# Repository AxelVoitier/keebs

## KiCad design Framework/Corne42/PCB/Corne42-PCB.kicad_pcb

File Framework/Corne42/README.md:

# Corne42 / Framework 16 — design review prototype

**Not released for fabrication, assembly, flashing or installation. No physical prototype has been tested.**

This is an AI-assisted derivative of Axel Voitier's HandyWork and A1 templates,
with 42 One Key Modules in a Corne-inspired layout: 3 × 6 keys plus 3 thumb keys
per hand. It uses OKMs, **not Choc switches**. The Corne Chocolate reference supplies
key positions; the controller and electrical design come from HandyWork.
Horizontal pitch is increased from 19.05 to 20.30 mm to avoid OKM pad/tab collisions;
vertical pitch remains 19.05 mm, with each half shifted inward by 2 mm. This is
not an exact reproduction of every Corne variant or of its keycap dimensions.

KiCad rendering of the actual PCB and embedded OKM models. The aluminium top
plate and laptop chassis are not shown; this is not a photograph or a fit validation.

## Review entry points

- [Main PCB and schematic](PCB/Corne42-PCB.kicad_pro), with project-relative libraries
  in `../Corne42.pretty` and `../Corne42.kicad_sym`.
- [Aluminium plate](AluPlate/Corne42-AluPlate.kicad_pro).
- [Firmware source](Firmware), [matrix/LED mapping](Review/electrical-mapping.json).
- [DRC](Review/drc.json), [ERC](Review/erc.json), [plate DRC](Review/plate-drc.json).
- [Conditional height calculation](Review/height-budget-conditional.json),
  [aperture check](Review/plate-aperture-check.json).
- [BOM](Review/BOM-review-only.csv), [supplier CPL](Review/CPL-review-only.csv),
  [controller underside](Review/controller-assembly-detail.svg), all **review only**.

The existing HandyWork files and shared Framework libraries are unchanged.
The local footprint variants preserve the per-component geometry used in the
reviewed board; they are supplied for library parity, not as new general-purpose
footprints. The corrected OKM footprint from upstream main is the starting point.

## Digital evidence and its limits

KiCad 10.0.7: **zero DRC errors, zero unconnected items, zero schematic/PCB parity
violations and zero ERC errors** in the supplied reports. These are design-rule
and consistency results, not proof of functional hardware.

The 42 DRC warnings report mixed SMD signal pads and plated mechanical slots on
OKMs. The 24 ERC warnings report inherited `C_Small` library differences; the
prior review compared pin geometry and types. The reports retain these warnings.
The main board report has no ignored checks. The plate retains its inherited
ignored-check list, visible in its report. No findings are hidden by this PR.

The main PCB SHA256 is
`47739568c578cbd6d3d88ca0366ca4ee43947878c37bd59026879a236ae34019`;
the plate SHA256 is
`d6a3a7b0d626e86c300b75459d5cb854e0ef8071d36dce5748283f1038d9d137`.
The reports predate this packaging step; the native design files are byte-identical
to those checked. Fresh portability checks are documented in `Review/portability.json`.

## Questions before spending money on a prototype

1. **Mechanical seating and height are unresolved.** A conditional comparison of
   the OKM model with Framework's simplified carrier puts its underside 0.70 mm
   beyond a representative main-field boundary. Another calculated placement
   leaves only about 0.055 mm nominal vertical slack, before tolerances, solder,
   adhesive, insulation and flex. These are not verified support positions or a
   full 42-key collision test. The OKM contact-plane datum, actual PCB supports,
   pogo travel, underside clearance and lid clearance need independent review.
   No support-height change is proposed as a fix without those measurements.
2. **Finished thickness:** proposed main PCB 0.8 mm, 4 layers, ENIG; plate 0.8 mm
   aluminium-base PCB with copper on the bottom only, following the original
   build. The inherited main CAD stack totals 0.8192 mm and the plate has a
   1 mm/FR4 placeholder. These metadata are not a qualified fabrication stack.
   An explicit manufacturer stack and tolerances must replace the placeholders
   before release. Nominal 0.8 mm alone does not prove fit.
3. **Via process and assembly:** 40 drilled 0.30 mm holes overlap stencil openings
   ([coordinates](Review/paste-overlapping-drills.csv)). Filled/capped was a
   conservative quotation choice, not an established requirement from Axel.
   Can the original plugged/tented process be qualified here? The 168 plated
   mechanical slots and 6 positioning holes must remain open. Supplier-rendered
   component orientation still needs confirmation. CPL already includes C25/C26
   +180°, U2 −90°, R12 +90° corrections; do not apply them twice.
4. **Functional behavior:** matrix/LED wiring, boot/recovery, independent SLEEP#
   and USB suspend, resume and current consumption need a real prototype.
   LED shutdown does not establish the whole-board sleep-current requirement.

The BOM has 48 controller-side components; 42 OKMs are fitted separately. R4/R5
retain the upstream description `27.4` with part C25190 (27 Ω). This inherited
metadata discrepancy is documented, not silently changed. Raspberry Pi's RP2040
hardware guide specifies 27 Ω USB series resistors; confirm and reconcile the
schematic/BOM labels before release.

## Reproduce the basic checks

Open the project with KiCad 10.0.7 and its standard symbol/footprint libraries.
Some inherited 3D references use `KICAD9_3DMODEL_DIR`; point this variable to the
installed KiCad 3D library if needed. The OKM model is embedded.
Keep macOS AppleDouble files (`._*`) out of the footprint libraries: during the
external-drive portability check, those metadata sidecars caused KiCad to report
the local libraries as unavailable. They are not part of this contribution.

From this directory, write fresh outputs outside the supplied review reports:

```sh
kicad-cli pcb drc --refill-zones --schematic-parity --severity-all --format json -o /tmp/corne42-drc.json PCB/Corne42-PCB.kicad_pcb
kicad-cli sch erc --severity-all --format json -o /tmp/corne42-erc.json PCB/Corne42-PCB.kicad_sch
kicad-cli pcb drc --severity-all --format json -o /tmp/corne42-plate-drc.json AluPlate/Corne42-AluPlate.kicad_pcb
```

Firmware was compiled and the ELF/UF2 correspondence checked with QMK revision
`6c8852ebb00a7d3a02040e29363ce7779627125a`. See
[build evidence](Review/firmware-build.json) for source hashes and binary hashes.
Copy `Firmware/` to `keyboards/handywork/corne42/` in that QMK checkout and run
`qmk compile -kb handywork/corne42 -km default` with the required toolchain.
No binary is offered as hardware-tested. The unchanged historical firmware README
and build report refer to earlier workspace paths/status; the evidence lives in
`Review/` here, and the current hardware status is this document.
The default keymap is a demonstration US QWERTY layout, not a personal keymap.
The prototype retains the upstream USB VID/PID; no new allocation is claimed.

## Lower-cost checks and first physical test

Before ordering assembled boards, print the layout at 100% with page fitting
disabled and verify its 50 mm scale bar. This can check hand position and gross
outline only. A non-powered mechanical mock-up or a small OKM soldering coupon
can help check contact-plane height, retention, apertures and solder behavior;
neither proves this full PCB works. Test supports and clearance with the actual
modules before trying to close the laptop lid.

After mechanical review, inspect a first board for shorts and assembly defects,
then use an appropriate current-limited bench fixture implementing the Framework
interface's separate supplies, ID and sleep signals. Verify boot/USB before
fitting all OKMs, then every key/LED, simultaneous keys, suspend/resume and measured
current on both supply rails. Only then test in the laptop. This protocol has
**not** been executed. A normal USB cable is not a complete Framework test fixture.

## Provenance and licensing

- [AxelVoitier/keebs](https://github.com/AxelVoitier/keebs/tree/5f5d24e842c48da215a0f635155b18f1e9b098e9):
  HandyWork templates, electronics, corrected OKM footprint, plate approach.
  See the repository's `LICENSES.txt`, CERN-OHL-W-2.0 and Framework footprint
  CERN-OHL-P-2.0 notices. Existing authorship/attribution is retained.
- [foostan/crkbd](https://github.com/foostan/crkbd/tree/63366fb7f51cf2a796462fdd90527e99dd126055):
  Corne Chocolate 4.1.0 key-centre reference, modified as described above.
  Copyright foostan; upstream MIT and CC BY 4.0 texts are included under `Licenses/`.
- [Axel's QMK branch](https://github.com/AxelVoitier/qmk_firmware/tree/axel/handywork/keyboards/handywork/5x3_mods_nav):
  firmware reference; QMK-derived source remains under GPL-2.0-or-later.
- [Framework input-module reference](https://github.com/FrameworkComputer/InputModules/tree/8d101b479ea4700ed1b758fd7ba3bd6b5ed75317):
  A1 design-space STEP/drawing, simplified 0.8 mm carrier and OKM drawing used for
  the conditional height analysis. These do not certify this assembly.
- [Axel's original prototype](https://community.frame.work/t/handywork-an-ergo-keyboard-for-the-framework-16/80180/18)
  is useful physical evidence for HandyWork, not a validation of this derivative.
- [RP2040 hardware design guide](https://datasheets.raspberrypi.com/rp2040/hardware-design-with-rp2040.pdf).

New hardware modifications follow the upstream hardware licensing; inherited
third-party material retains its applicable license. This submission is for
technical review and is not a manufacturing release.

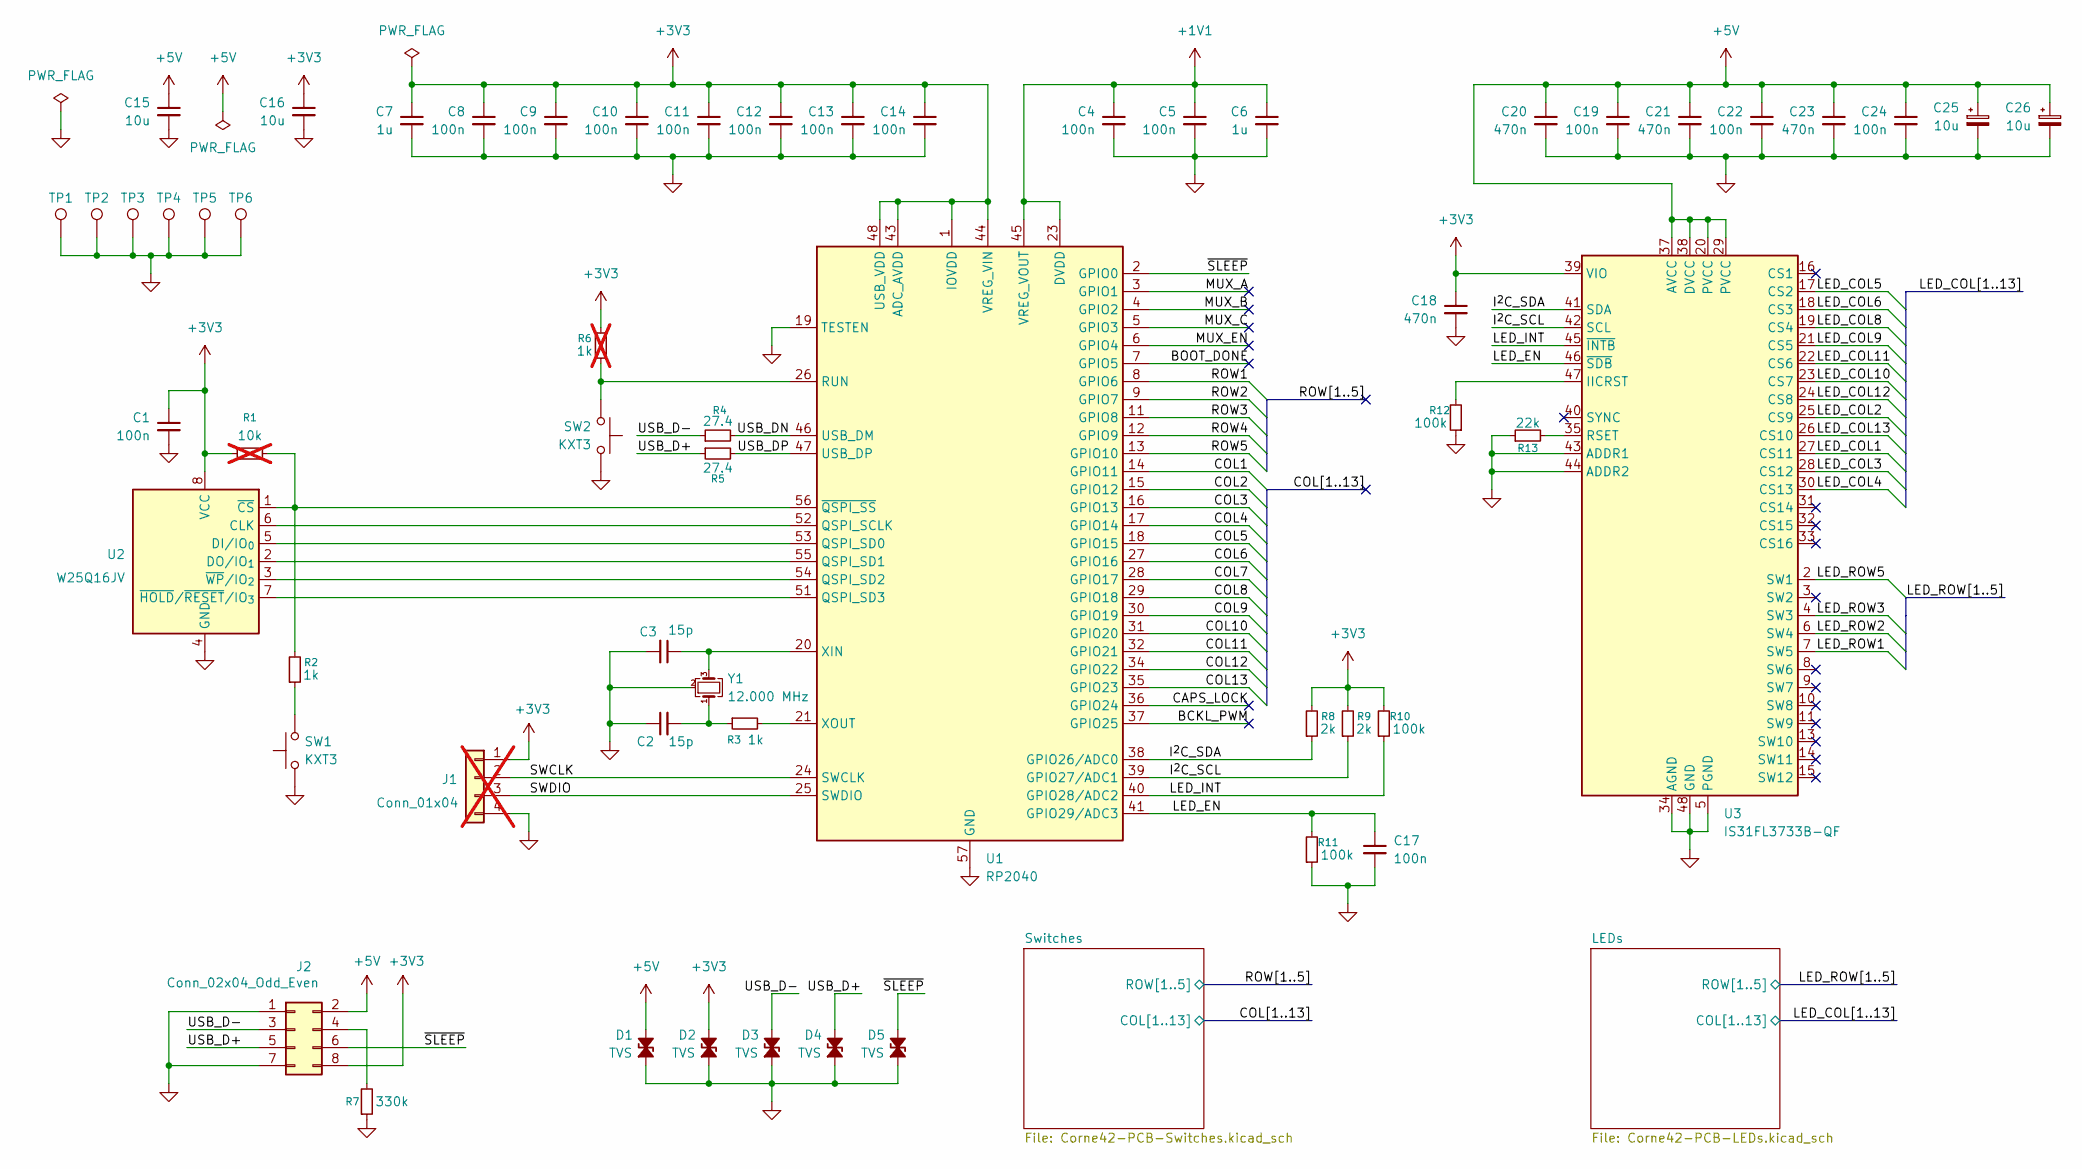
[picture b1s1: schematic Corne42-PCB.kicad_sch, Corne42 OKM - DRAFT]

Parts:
C1, C4, C5, C8, C9, C10, C11, C12, C13, C14, C17, C19, C22, C24: 100n; C_0402_1005Metric; LCSC C1525
C2, C3: 15p; C_0402_1005Metric; LCSC C1548
C6, C7: 1u; C_0402_1005Metric; LCSC C52923
C15, C16: 10u; C_0603_1608Metric; LCSC C19702
C18, C20, C21, C23: 470n; C_0603_1608Metric; LCSC C1623
C25: 10u; CP_EIA-3216-18_Kemet-A_HandSolder_Corne42_C25; LCSC C7171
C26: 10u; CP_EIA-3216-18_Kemet-A_HandSolder_Corne42_C26; LCSC C7171
D1, D2, D3, D4, D5: TVS; D_SOD-523; LCSC C20615820
J1: Conn_01x04; PinHeader_1x04_P1.00mm_Vertical; not fitted
J2: Conn_02x04_Odd_Even; A1 Board PCB
R1: 10k; R_0402_1005Metric_Corne42_R1; LCSC C25744; not fitted
R2, R3: 1k; R_0402_1005Metric; LCSC C11702
R4, R5: 27.4; R_0603_1608Metric; LCSC C25190
R6: 1k; R_0402_1005Metric_Corne42_R6; LCSC C11702; not fitted
R7: 330k; R_0603_1608Metric; LCSC C23137
R8, R9: 2k; R_0402_1005Metric; LCSC C4109
R10, R11, R12: 100k; R_0402_1005Metric; LCSC C25741
R13: 22k; R_0805_2012Metric_Pad1.20x1.40mm_HandSolder; LCSC C17560
SW1: KXT3; SW_SPST_CK_KXT3; MPN KXT331LHS; Mouser 611-KXT331LHS
SW2: KXT3; SW_SPST_CK_KXT3; MPN KXT331LHS; Digikey CKN10779CT-ND
TP1, TP2, TP3, TP4, TP5, TP6: TestPoint; TestPoint_THTPad_2.5x2.5mm_Drill1.2mm
U1: RP2040; QFN-56-1EP_7x7mm_P0.4mm_EP3.2x3.2mm_ThermalVias_Corne42_U1; MPN SC0914(13); Mouser 358-SC091413
U2: W25Q16JV; Winbond_USON-8-1EP_3x2mm_P0.5mm_EP0.2x1.6mm; MPN W25Q16JVUXIQ; Mouser 454-W25Q16JVUXIQTR
U3: IS31FL3733B-QF; QFN-48-1EP_6x6mm_P0.4mm_EP4.2x4.2mm_ThermalVias_Corne42_U3; MPN IS31FL3733B-QFLS4-TR; Mouser 870-IS31FL3733BQFLS4
Y1: 12.000 MHz; Crystal_SMD_Abracon_ABM8AIG-4Pin_3.2x2.5mm; MPN ABM8-272-T3; Mouser 815-ABM8-272-T3

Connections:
+1V1: C4.1, C5.1, C6.1, U1.23 (DVDD), U1.45 (VREG_VOUT), U1.50 (DVDD)
+3V3: C1.1, C7.1, C8.1, C9.1, C10.1, C11.1, C12.1, C13.1, C14.1, C16.1, C18.1, D2.2 (A2), J1.1, J2.8, R1.1, R6.2, R8.2, R9.2, R10.2, U1.1 (IOVDD), U1.10 (IOVDD), U1.22 (IOVDD), U1.33 (IOVDD), U1.42 (IOVDD), U1.43 (ADC_AVDD), U1.44 (VREG_VIN), U1.48 (USB_VDD), U1.49 (IOVDD), U2.8 (VCC), U3.39 (VIO)
+5V: C15.1, C19.1, C20.1, C21.1, C22.1, C23.1, C24.1, C25.1, C26.1, D1.2 (A2), J2.2, U3.20 (PVCC), U3.29 (PVCC), U3.37 (AVCC), U3.38 (DVCC)
/BCKL_PWM: U1.37 (GPIO25)
/BOOT_DONE: U1.7 (GPIO5)
/CAPS_LOCK: U1.36 (GPIO24)
/COL1: U1.14 (GPIO11); also elsewhere on the board
/COL2: U1.15 (GPIO12); also elsewhere on the board
/COL3: U1.16 (GPIO13); also elsewhere on the board
/COL4: U1.17 (GPIO14); also elsewhere on the board
/COL5: U1.18 (GPIO15); also elsewhere on the board
/COL6: U1.27 (GPIO16); also elsewhere on the board
/COL7: U1.28 (GPIO17)
/COL8: U1.29 (GPIO18); also elsewhere on the board
/COL9: U1.30 (GPIO19); also elsewhere on the board
/COL10: U1.31 (GPIO20); also elsewhere on the board
/COL11: U1.32 (GPIO21); also elsewhere on the board
/COL12: U1.34 (GPIO22); also elsewhere on the board
/COL13: U1.35 (GPIO23); also elsewhere on the board
/I^{2}C_SCL: R9.1, U1.39 (GPIO27/ADC1), U3.42 (SCL)
/I^{2}C_SDA: R8.1, U1.38 (GPIO26/ADC0), U3.41 (SDA)
/LED_COL1: U3.27 (CS11); also elsewhere on the board
/LED_COL2: U3.25 (CS9); also elsewhere on the board
/LED_COL3: U3.28 (CS12); also elsewhere on the board
/LED_COL4: U3.30 (CS13); also elsewhere on the board
/LED_COL5: U3.17 (CS2); also elsewhere on the board
/LED_COL6: U3.18 (CS3); also elsewhere on the board
/LED_COL8: U3.19 (CS4); also elsewhere on the board
/LED_COL9: U3.21 (CS5); also elsewhere on the board
/LED_COL10: U3.23 (CS7); also elsewhere on the board
/LED_COL11: U3.22 (CS6); also elsewhere on the board
/LED_COL12: U3.24 (CS8); also elsewhere on the board
/LED_COL13: U3.26 (CS10); also elsewhere on the board
/LED_EN: C17.1, R11.2, U1.41 (GPIO29/ADC3), U3.46 (~SDB)
/LED_INT: R10.1, U1.40 (GPIO28/ADC2), U3.45 (~INTB)
/LED_ROW1: U3.7 (SW5); also elsewhere on the board
/LED_ROW2: U3.6 (SW4); also elsewhere on the board
/LED_ROW3: U3.4 (SW3); also elsewhere on the board
/LED_ROW5: U3.2 (SW1); also elsewhere on the board
/MUX_A: U1.3 (GPIO1)
/MUX_B: U1.4 (GPIO2)
/MUX_C: U1.5 (GPIO3)
/MUX_EN: U1.6 (GPIO4)
/ROW1: U1.8 (GPIO6); also elsewhere on the board
/ROW2: U1.9 (GPIO7); also elsewhere on the board
/ROW3: U1.11 (GPIO8); also elsewhere on the board
/ROW4: U1.12 (GPIO9)
/ROW5: U1.13 (GPIO10); also elsewhere on the board
/SWCLK: J1.2, U1.24 (SWCLK)
/SWDIO: J1.3, U1.25 (SWDIO)
/USB_D+: D4.2 (A2), J2.5, R5.1
/USB_D-: D3.2 (A2), J2.3, R4.1
/USB_DN: R4.2, U1.46 (USB_DM)
/USB_DP: R5.2, U1.47 (USB_DP)
/~SLEEP: D5.2 (A2), J2.6, U1.2 (GPIO0)
GND: C1.2, C2.1, C3.2, C4.2, C5.2, C6.2, C7.2, C8.2, C9.2, C10.2, C11.2, C12.2, C13.2, C14.2, C15.2, C16.2, C17.2, C18.2, C19.2, C20.2, C21.2, C22.2, C23.2, C24.2, C25.2, C26.2, D1.1 (A1), D2.1 (A1), D3.1 (A1), D4.1 (A1), D5.1 (A1), J1.4, J2.1, J2.7, R7.1, R11.1, R12.1, R13.1, SW1.1, SW2.1, TP1.1, TP2.1, TP3.1, TP4.1, TP5.1, TP6.1, U1.19 (TESTEN), U1.57 (GND), U2.4 (GND), U2.9 (EP), U3.5 (PGND), U3.12 (PGND), U3.34 (AGND), U3.43 (ADDR1), U3.44 (ADDR2), U3.48 (GND), U3.49 (GND), Y1.2 (G), Y1.4 (G); also elsewhere on the board
unnamed: C2.2, R3.1, Y1.1
unnamed: J2.4, R7.2
unnamed: R2.1, SW1.2
unnamed: U1.52 (QSPI_SCLK), U2.6 (CLK)
unnamed: U1.53 (QSPI_SD0), U2.5 (DI/IO_{0})
unnamed: U1.55 (QSPI_SD1), U2.2 (DO/IO_{1})
unnamed: U1.54 (QSPI_SD2), U2.3 (~WP/IO_{2})
unnamed: U1.51 (QSPI_SD3), U2.7 (~HOLD/~RESET/IO_{3})
unnamed: R6.1, SW2.2, U1.26 (RUN)
unnamed: C3.1, U1.20 (XIN), Y1.3
unnamed: R3.2, U1.21 (XOUT)
unnamed: R1.2, R2.2, U1.56 (~QSPI_SS), U2.1 (~CS)
unnamed: R12.2, U3.47 (IICRST)
unnamed: R13.2, U3.35 (RSET)

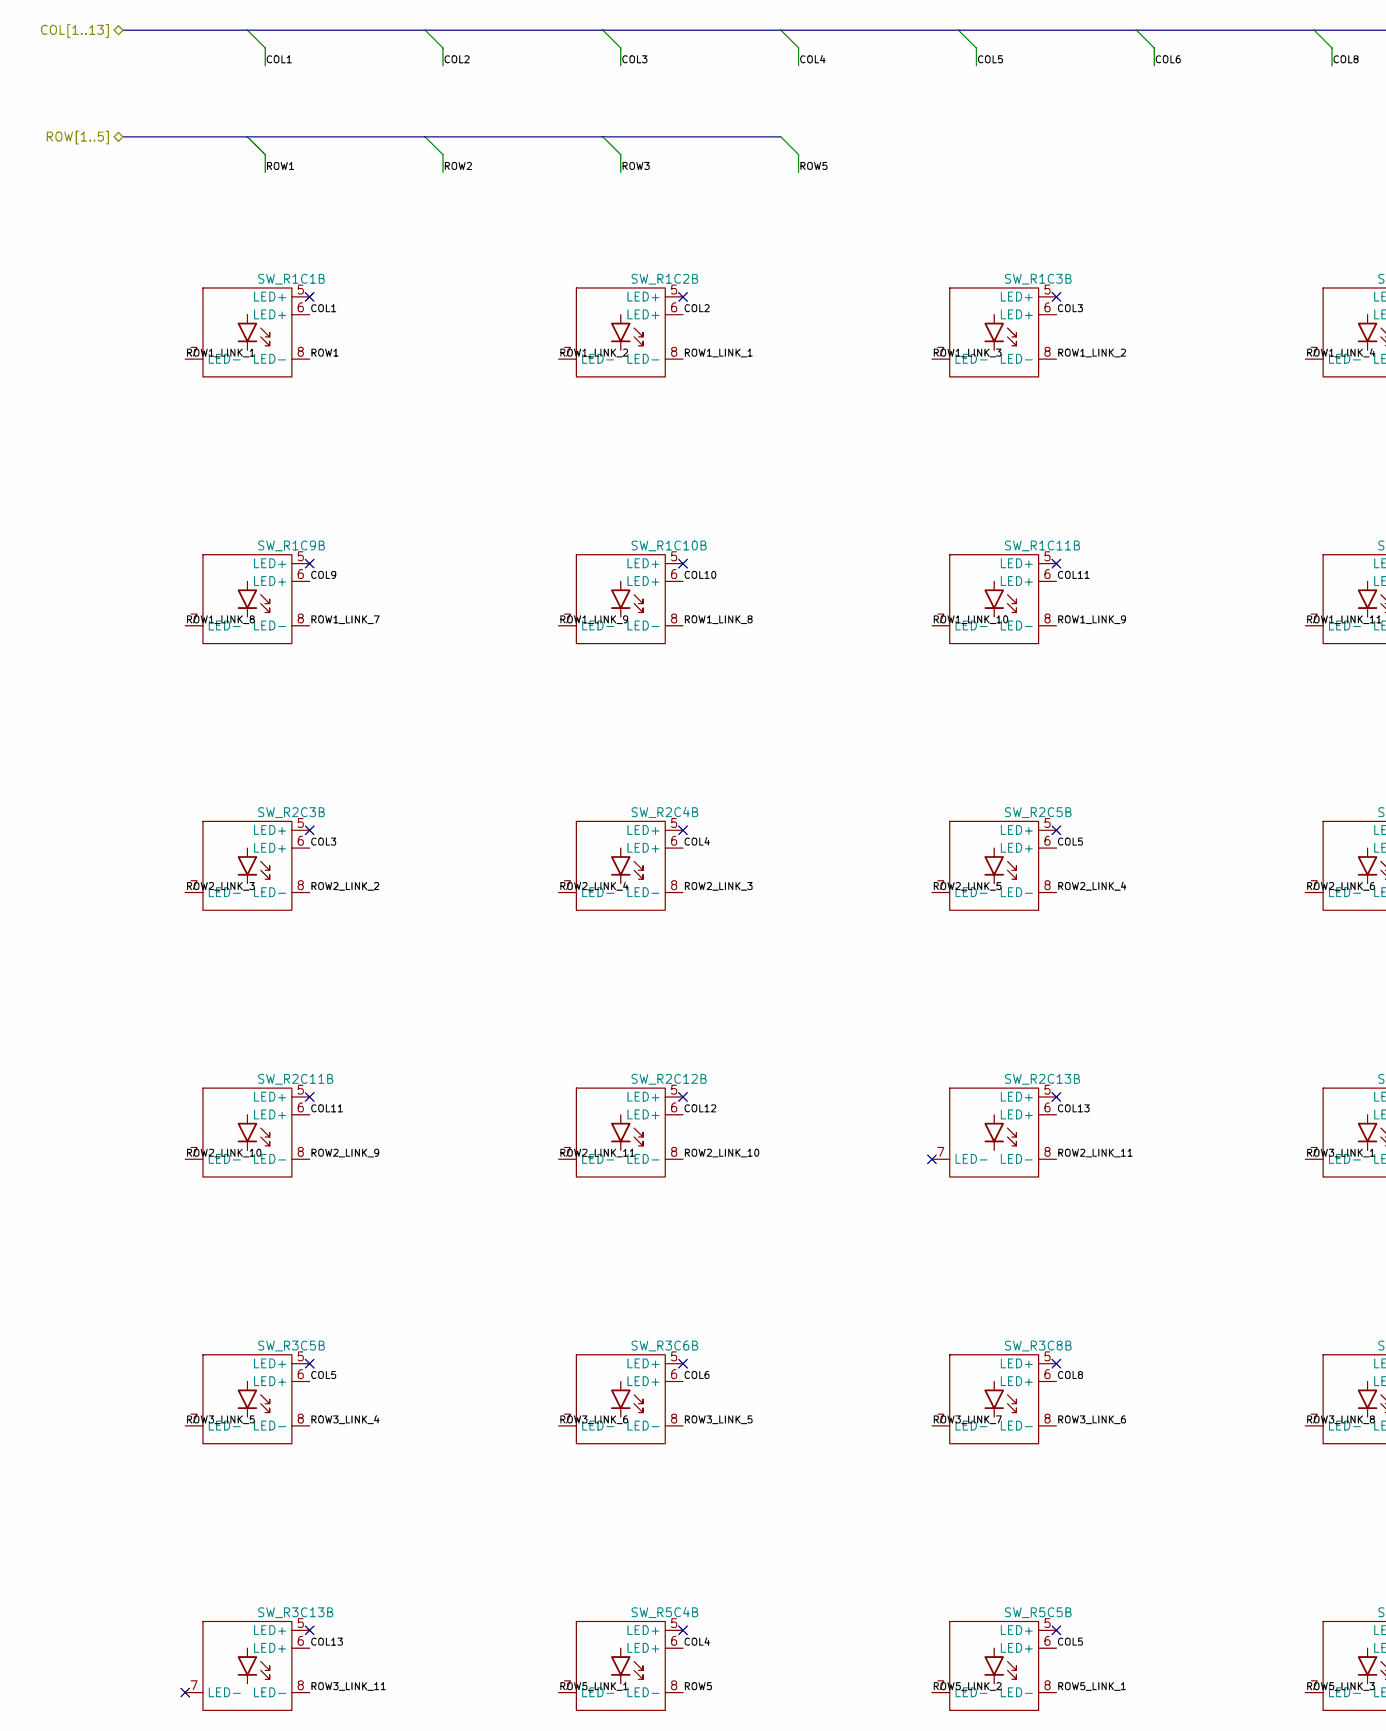
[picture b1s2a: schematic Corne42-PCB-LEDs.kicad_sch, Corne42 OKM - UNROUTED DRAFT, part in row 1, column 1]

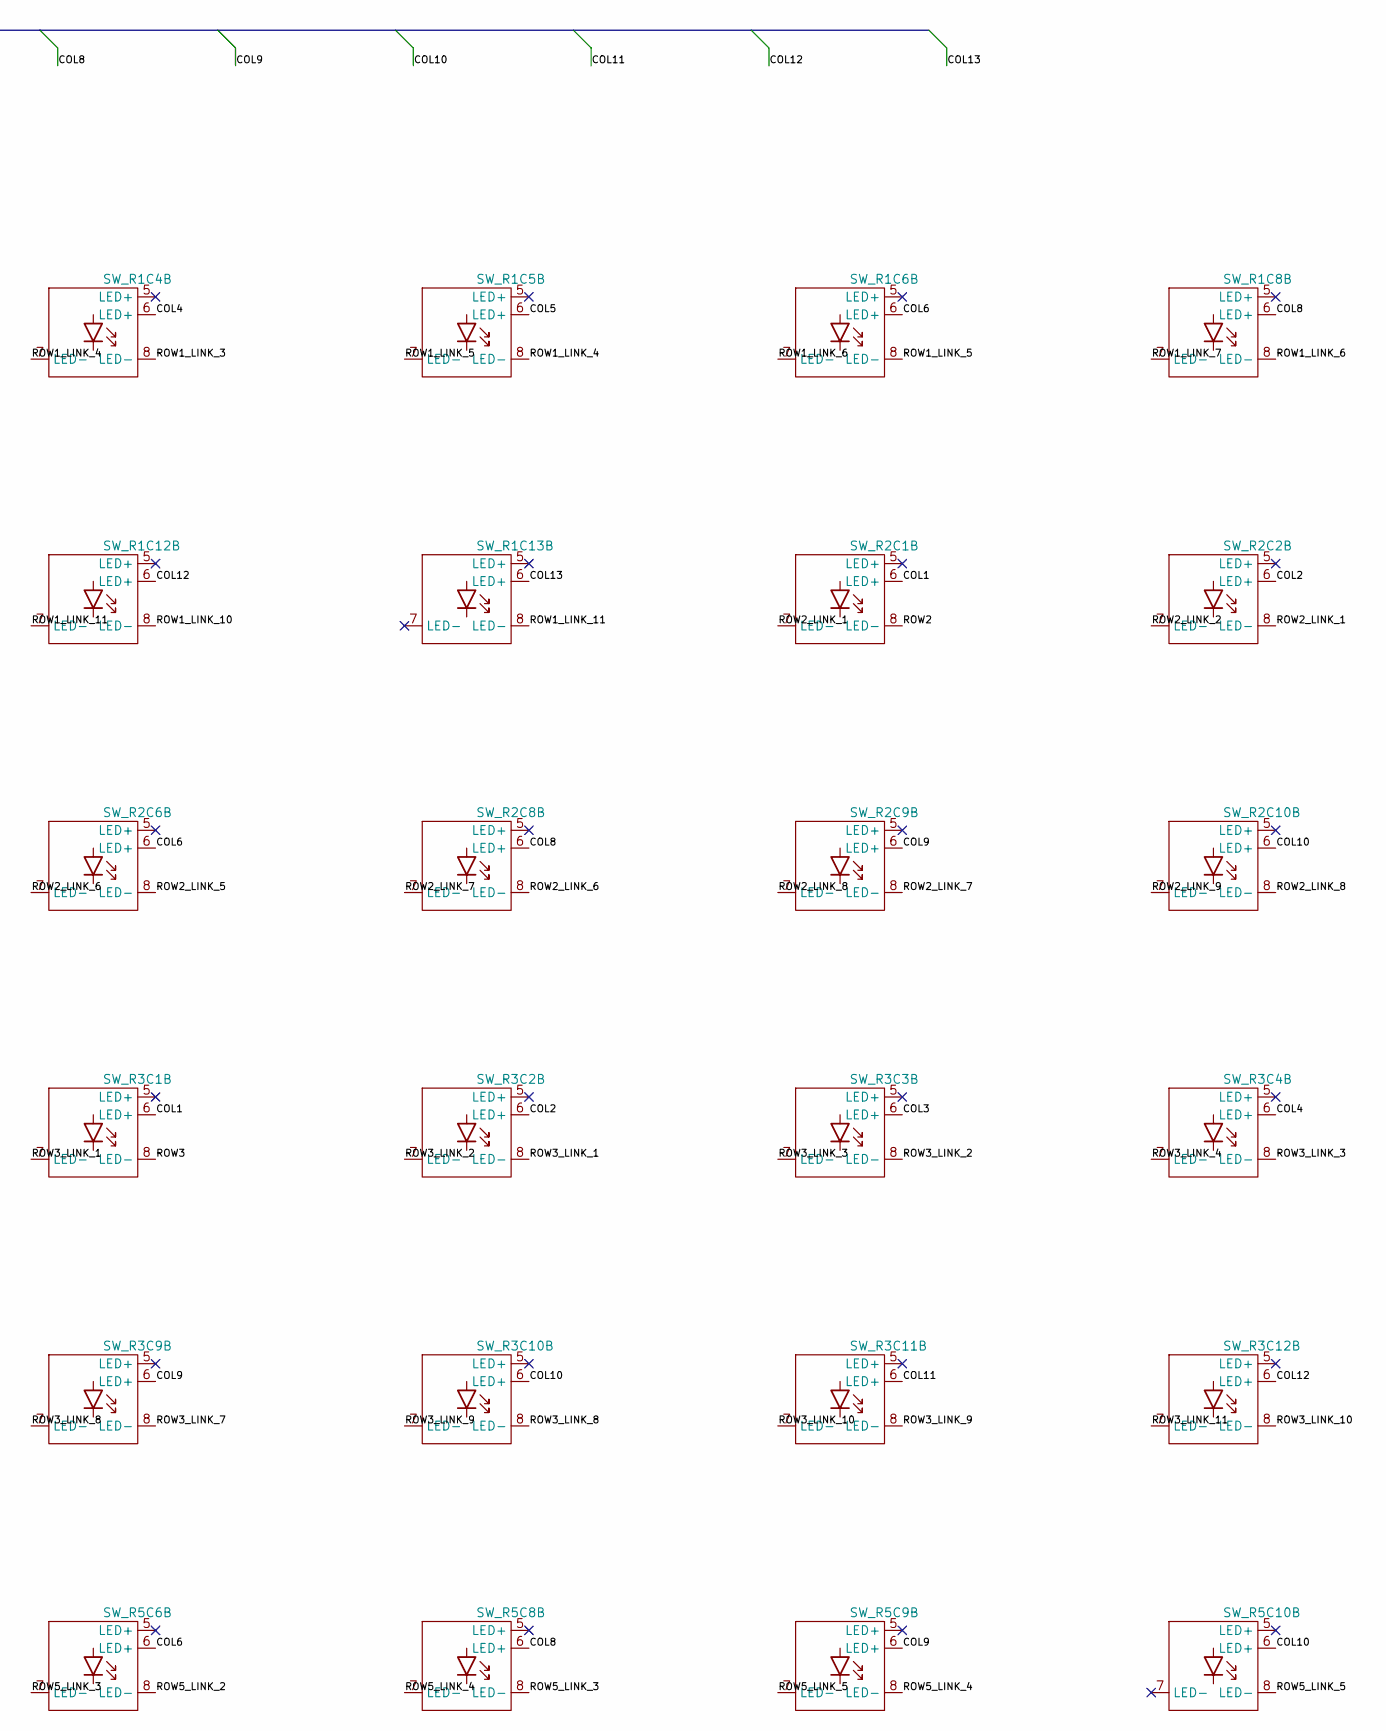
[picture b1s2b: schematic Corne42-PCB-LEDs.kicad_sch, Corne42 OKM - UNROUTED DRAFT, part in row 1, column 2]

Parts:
SW_R1C1: One Key Module_Corne42_SW_R1C1
SW_R1C2: One Key Module_Corne42_SW_R1C2
SW_R1C3: One Key Module_Corne42_SW_R1C3
SW_R1C4: One Key Module_Corne42_SW_R1C4
SW_R1C5: One Key Module_Corne42_SW_R1C5
SW_R1C6: One Key Module_Corne42_SW_R1C6
SW_R1C8: One Key Module_Corne42_SW_R1C8
SW_R1C9: One Key Module_Corne42_SW_R1C9
SW_R1C10: One Key Module_Corne42_SW_R1C10
SW_R1C11: One Key Module_Corne42_SW_R1C11
SW_R1C12: One Key Module_Corne42_SW_R1C12
SW_R1C13: One Key Module_Corne42_SW_R1C13
SW_R2C1: One Key Module_Corne42_SW_R2C1
SW_R2C2: One Key Module_Corne42_SW_R2C2
SW_R2C3: One Key Module_Corne42_SW_R2C3
SW_R2C4: One Key Module_Corne42_SW_R2C4
SW_R2C5: One Key Module_Corne42_SW_R2C5
SW_R2C6: One Key Module_Corne42_SW_R2C6
SW_R2C8: One Key Module_Corne42_SW_R2C8
SW_R2C9: One Key Module_Corne42_SW_R2C9
SW_R2C10: One Key Module_Corne42_SW_R2C10
SW_R2C11: One Key Module_Corne42_SW_R2C11
SW_R2C12: One Key Module_Corne42_SW_R2C12
SW_R2C13: One Key Module_Corne42_SW_R2C13
SW_R3C1: One Key Module_Corne42_SW_R3C1
SW_R3C2: One Key Module_Corne42_SW_R3C2
SW_R3C3: One Key Module_Corne42_SW_R3C3
SW_R3C4: One Key Module_Corne42_SW_R3C4
SW_R3C5: One Key Module_Corne42_SW_R3C5
SW_R3C6: One Key Module_Corne42_SW_R3C6
SW_R3C8: One Key Module_Corne42_SW_R3C8
SW_R3C9: One Key Module_Corne42_SW_R3C9
SW_R3C10: One Key Module_Corne42_SW_R3C10
SW_R3C11: One Key Module_Corne42_SW_R3C11
SW_R3C12: One Key Module_Corne42_SW_R3C12
SW_R3C13: One Key Module_Corne42_SW_R3C13
SW_R5C4: One Key Module_Corne42_SW_R5C4
SW_R5C5: One Key Module_Corne42_SW_R5C5
SW_R5C6: One Key Module_Corne42_SW_R5C6
SW_R5C8: One Key Module_Corne42_SW_R5C8
SW_R5C9: One Key Module_Corne42_SW_R5C9
SW_R5C10: One Key Module_Corne42_SW_R5C10

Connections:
/LED_COL1: SW_R1C1.6 (LED+), SW_R2C1.6 (LED+), SW_R3C1.6 (LED+); also elsewhere on the board
/LED_COL2: SW_R1C2.6 (LED+), SW_R2C2.6 (LED+), SW_R3C2.6 (LED+); also elsewhere on the board
/LED_COL3: SW_R1C3.6 (LED+), SW_R2C3.6 (LED+), SW_R3C3.6 (LED+); also elsewhere on the board
/LED_COL4: SW_R1C4.6 (LED+), SW_R2C4.6 (LED+), SW_R3C4.6 (LED+), SW_R5C4.6 (LED+); also elsewhere on the board
/LED_COL5: SW_R1C5.6 (LED+), SW_R2C5.6 (LED+), SW_R3C5.6 (LED+), SW_R5C5.6 (LED+); also elsewhere on the board
/LED_COL6: SW_R1C6.6 (LED+), SW_R2C6.6 (LED+), SW_R3C6.6 (LED+), SW_R5C6.6 (LED+); also elsewhere on the board
/LED_COL8: SW_R1C8.6 (LED+), SW_R2C8.6 (LED+), SW_R3C8.6 (LED+), SW_R5C8.6 (LED+); also elsewhere on the board
/LED_COL9: SW_R1C9.6 (LED+), SW_R2C9.6 (LED+), SW_R3C9.6 (LED+), SW_R5C9.6 (LED+); also elsewhere on the board
/LED_COL10: SW_R1C10.6 (LED+), SW_R2C10.6 (LED+), SW_R3C10.6 (LED+), SW_R5C10.6 (LED+); also elsewhere on the board
/LED_COL11: SW_R1C11.6 (LED+), SW_R2C11.6 (LED+), SW_R3C11.6 (LED+); also elsewhere on the board
/LED_COL12: SW_R1C12.6 (LED+), SW_R2C12.6 (LED+), SW_R3C12.6 (LED+); also elsewhere on the board
/LED_COL13: SW_R1C13.6 (LED+), SW_R2C13.6 (LED+), SW_R3C13.6 (LED+); also elsewhere on the board
/LED_ROW1: SW_R1C1.8 (LED-); also elsewhere on the board
/LED_ROW2: SW_R2C1.8 (LED-); also elsewhere on the board
/LED_ROW3: SW_R3C1.8 (LED-); also elsewhere on the board
/LED_ROW5: SW_R5C4.8 (LED-); also elsewhere on the board
/LEDs/ROW1_LINK_1: SW_R1C1.7 (LED-), SW_R1C2.8 (LED-)
/LEDs/ROW1_LINK_2: SW_R1C2.7 (LED-), SW_R1C3.8 (LED-)
/LEDs/ROW1_LINK_3: SW_R1C3.7 (LED-), SW_R1C4.8 (LED-)
/LEDs/ROW1_LINK_4: SW_R1C4.7 (LED-), SW_R1C5.8 (LED-)
/LEDs/ROW1_LINK_5: SW_R1C5.7 (LED-), SW_R1C6.8 (LED-)
/LEDs/ROW1_LINK_6: SW_R1C6.7 (LED-), SW_R1C8.8 (LED-)
/LEDs/ROW1_LINK_7: SW_R1C8.7 (LED-), SW_R1C9.8 (LED-)
/LEDs/ROW1_LINK_8: SW_R1C9.7 (LED-), SW_R1C10.8 (LED-)
/LEDs/ROW1_LINK_9: SW_R1C10.7 (LED-), SW_R1C11.8 (LED-)
/LEDs/ROW1_LINK_10: SW_R1C11.7 (LED-), SW_R1C12.8 (LED-)
/LEDs/ROW1_LINK_11: SW_R1C12.7 (LED-), SW_R1C13.8 (LED-)
/LEDs/ROW2_LINK_1: SW_R2C1.7 (LED-), SW_R2C2.8 (LED-)
/LEDs/ROW2_LINK_2: SW_R2C2.7 (LED-), SW_R2C3.8 (LED-)
/LEDs/ROW2_LINK_3: SW_R2C3.7 (LED-), SW_R2C4.8 (LED-)
/LEDs/ROW2_LINK_4: SW_R2C4.7 (LED-), SW_R2C5.8 (LED-)
/LEDs/ROW2_LINK_5: SW_R2C5.7 (LED-), SW_R2C6.8 (LED-)
/LEDs/ROW2_LINK_6: SW_R2C6.7 (LED-), SW_R2C8.8 (LED-)
/LEDs/ROW2_LINK_7: SW_R2C8.7 (LED-), SW_R2C9.8 (LED-)
/LEDs/ROW2_LINK_8: SW_R2C9.7 (LED-), SW_R2C10.8 (LED-)
/LEDs/ROW2_LINK_9: SW_R2C10.7 (LED-), SW_R2C11.8 (LED-)
/LEDs/ROW2_LINK_10: SW_R2C11.7 (LED-), SW_R2C12.8 (LED-)
/LEDs/ROW2_LINK_11: SW_R2C12.7 (LED-), SW_R2C13.8 (LED-)
/LEDs/ROW3_LINK_1: SW_R3C1.7 (LED-), SW_R3C2.8 (LED-)
/LEDs/ROW3_LINK_2: SW_R3C2.7 (LED-), SW_R3C3.8 (LED-)
/LEDs/ROW3_LINK_3: SW_R3C3.7 (LED-), SW_R3C4.8 (LED-)
/LEDs/ROW3_LINK_4: SW_R3C4.7 (LED-), SW_R3C5.8 (LED-)
/LEDs/ROW3_LINK_5: SW_R3C5.7 (LED-), SW_R3C6.8 (LED-)
/LEDs/ROW3_LINK_6: SW_R3C6.7 (LED-), SW_R3C8.8 (LED-)
/LEDs/ROW3_LINK_7: SW_R3C8.7 (LED-), SW_R3C9.8 (LED-)
/LEDs/ROW3_LINK_8: SW_R3C9.7 (LED-), SW_R3C10.8 (LED-)
/LEDs/ROW3_LINK_9: SW_R3C10.7 (LED-), SW_R3C11.8 (LED-)
/LEDs/ROW3_LINK_10: SW_R3C11.7 (LED-), SW_R3C12.8 (LED-)
/LEDs/ROW3_LINK_11: SW_R3C12.7 (LED-), SW_R3C13.8 (LED-)
/LEDs/ROW5_LINK_1: SW_R5C4.7 (LED-), SW_R5C5.8 (LED-)
/LEDs/ROW5_LINK_2: SW_R5C5.7 (LED-), SW_R5C6.8 (LED-)
/LEDs/ROW5_LINK_3: SW_R5C6.7 (LED-), SW_R5C8.8 (LED-)
/LEDs/ROW5_LINK_4: SW_R5C8.7 (LED-), SW_R5C9.8 (LED-)
/LEDs/ROW5_LINK_5: SW_R5C9.7 (LED-), SW_R5C10.8 (LED-)

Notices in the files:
Framework/Corne42/README.md:
Provenance and licensing:
HandyWork templates, electronics, corrected OKM footprint, plate approach.
See the repository's `LICENSES.txt`, CERN-OHL-W-2.0 and Framework footprint
CERN-OHL-P-2.0 notices. Existing authorship/attribution is retained.
- [foostan/crkbd](https://github.com/foostan/crkbd/tree/63366fb7f51cf2a796462fdd90527e99dd126055):
Corne Chocolate 4.1.0 key-centre reference, modified as described above.
Copyright foostan; upstream MIT and CC BY 4.0 texts are included under `Licenses/`.
- [Ax
